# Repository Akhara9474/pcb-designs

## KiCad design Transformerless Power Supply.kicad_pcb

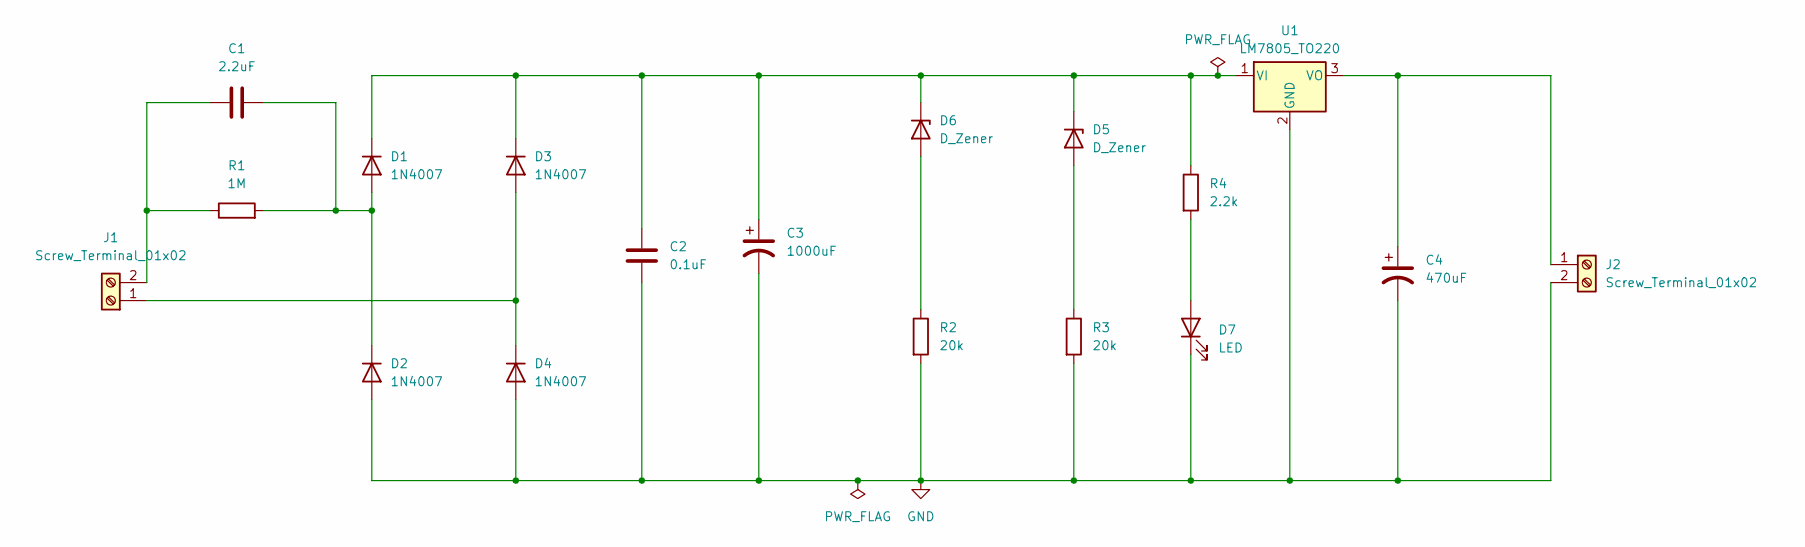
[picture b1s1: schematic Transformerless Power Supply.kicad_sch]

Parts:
C1: 2.2uF; C_Rect_L18.0mm_W6.0mm_P15.00mm_FKS3_FKP3
C2: 0.1uF; C_Disc_D4.7mm_W2.5mm_P5.00mm
C3: 1000uF; CP_Radial_D10.0mm_P5.00mm
C4: 470uF; CP_Radial_D10.0mm_P3.80mm
D1, D2, D3, D4: 1N4007; D_DO-41_SOD81_P10.16mm_Horizontal
D5, D6: D_Zener; D_A-405_P7.62mm_Horizontal
D7: LED; LED_D5.0mm
J1, J2: Screw_Terminal_01x02; Wuerth_691311400102_P7.62mm
R1: 1M; R_Axial_DIN0207_L6.3mm_D2.5mm_P7.62mm_Horizontal
R2, R3: 20k; R_Axial_DIN0207_L6.3mm_D2.5mm_P7.62mm_Horizontal
R4: 2.2k; R_Axial_DIN0207_L6.3mm_D2.5mm_P7.62mm_Horizontal
U1: LM7805_TO220; TO-220-3_Vertical

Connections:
GND: C2.1, C3.2, C4.2, D2.2 (A), D4.2 (A), D7.1 (K), J2.2, R2.2, R3.2, U1.2 (GND)
unnamed: C1.2, D1.2 (A), D2.1 (K), R1.2
unnamed: C2.2, C3.1, D1.1 (K), D3.1 (K), D5.1 (K), D6.1 (K), R4.1, U1.1 (VI)
unnamed: D3.2 (A), D4.1 (K), J1.1
unnamed: D5.2 (A), R3.1
unnamed: D6.2 (A), R2.1
unnamed: D7.2 (A), R4.2
unnamed: C1.1, J1.2, R1.1
unnamed: C4.1, J2.1, U1.3 (VO)

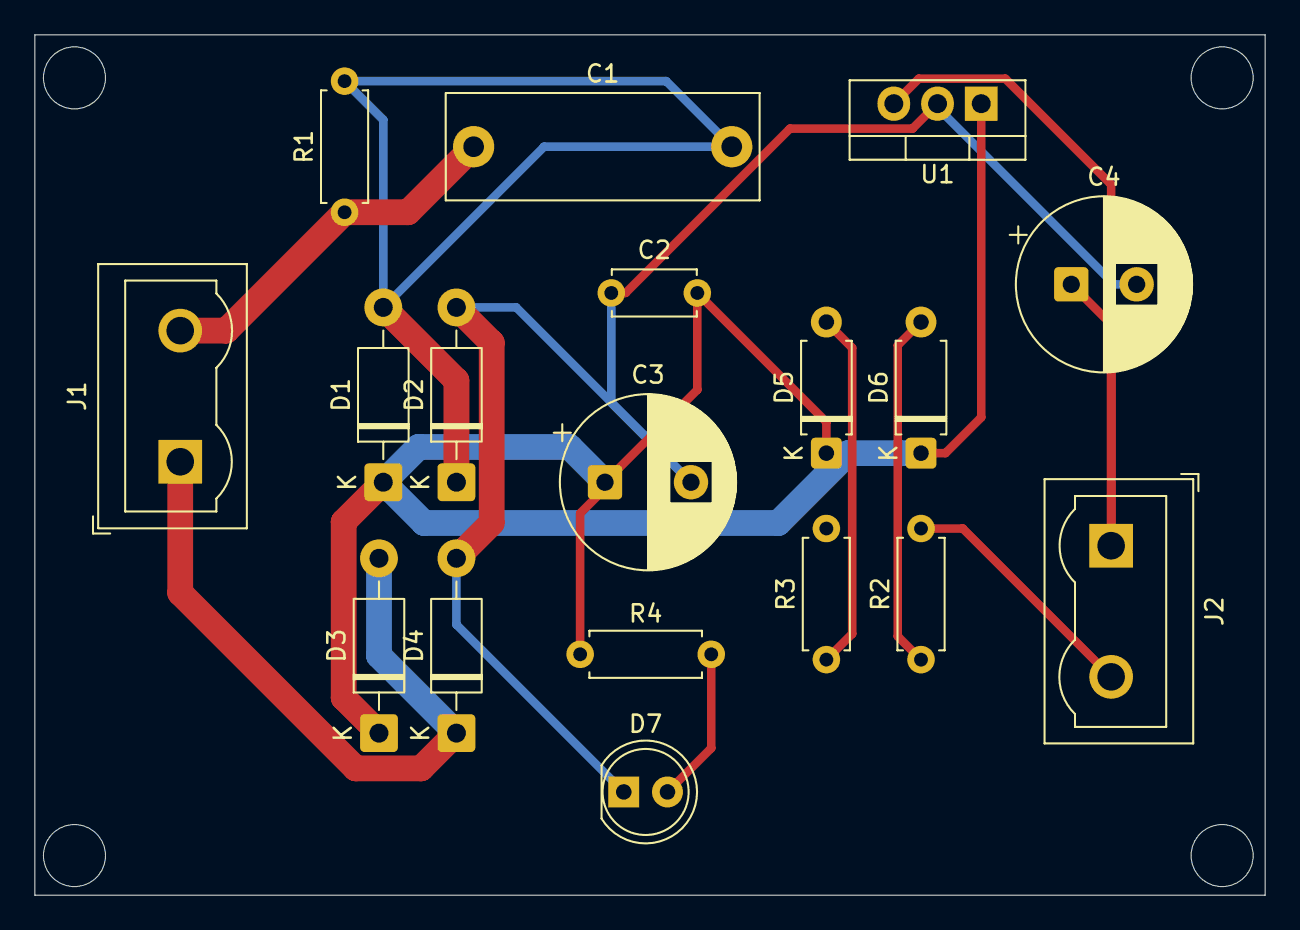
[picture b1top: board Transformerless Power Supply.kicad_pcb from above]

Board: 2 copper layers, 71.5 x 50.0 mm, 18 parts (0 on the bottom side), 9 nets.

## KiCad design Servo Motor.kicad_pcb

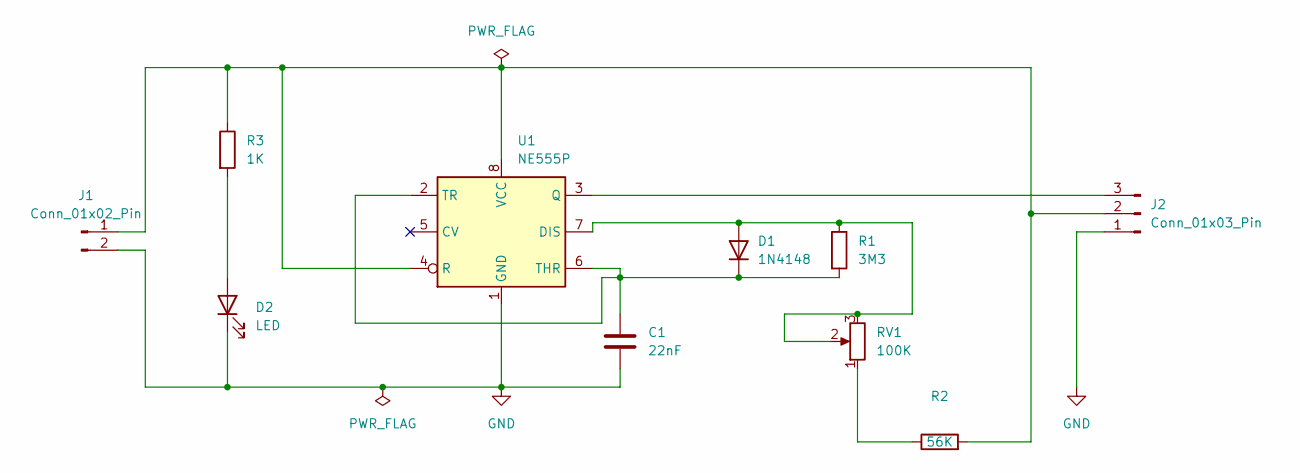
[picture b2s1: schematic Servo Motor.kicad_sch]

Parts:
C1: 22nF; C_Disc_D4.3mm_W1.9mm_P5.00mm
D1: 1N4148; D_DO-35_SOD27_P7.62mm_Horizontal
D2: LED; LED_D3.0mm
J1: Conn_01x02_Pin; PinHeader_1x02_P2.54mm_Horizontal
J2: Conn_01x03_Pin; PinHeader_1x03_P2.54mm_Horizontal
R1: 3M3; R_Axial_DIN0204_L3.6mm_D1.6mm_P7.62mm_Horizontal
R2: 56K; R_Axial_DIN0204_L3.6mm_D1.6mm_P7.62mm_Horizontal
R3: 1K; R_Axial_DIN0204_L3.6mm_D1.6mm_P7.62mm_Horizontal
RV1: 100K; Potentiometer_Alps_RK163_Single_Horizontal
U1: NE555P; DIP-8_W7.62mm

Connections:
GND: C1.1, D2.1 (K), J1.2, J2.1, U1.1 (GND)
unnamed: D1.2 (A), R1.1, RV1.2, RV1.3, U1.7 (DIS)
unnamed: C1.2, D1.1 (K), R1.2, U1.2 (TR), U1.6 (THR)
unnamed: D2.2 (A), R3.2
unnamed: J1.1, J2.2, R2.2, R3.1, U1.4 (R), U1.8 (VCC)
unnamed: J2.3, U1.3 (Q)
unnamed: R2.1, RV1.1

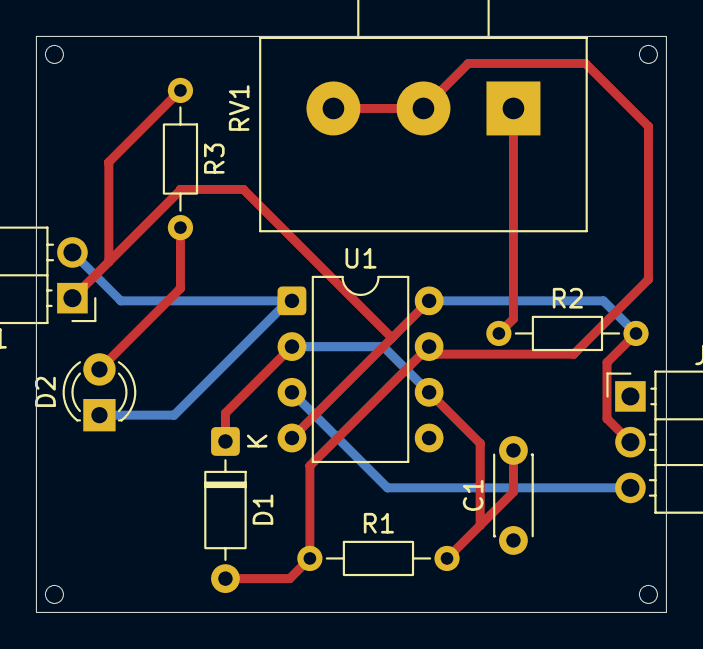
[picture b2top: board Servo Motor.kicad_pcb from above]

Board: 2 copper layers, 35.0 x 32.0 mm, 10 parts (0 on the bottom side), 7 nets.

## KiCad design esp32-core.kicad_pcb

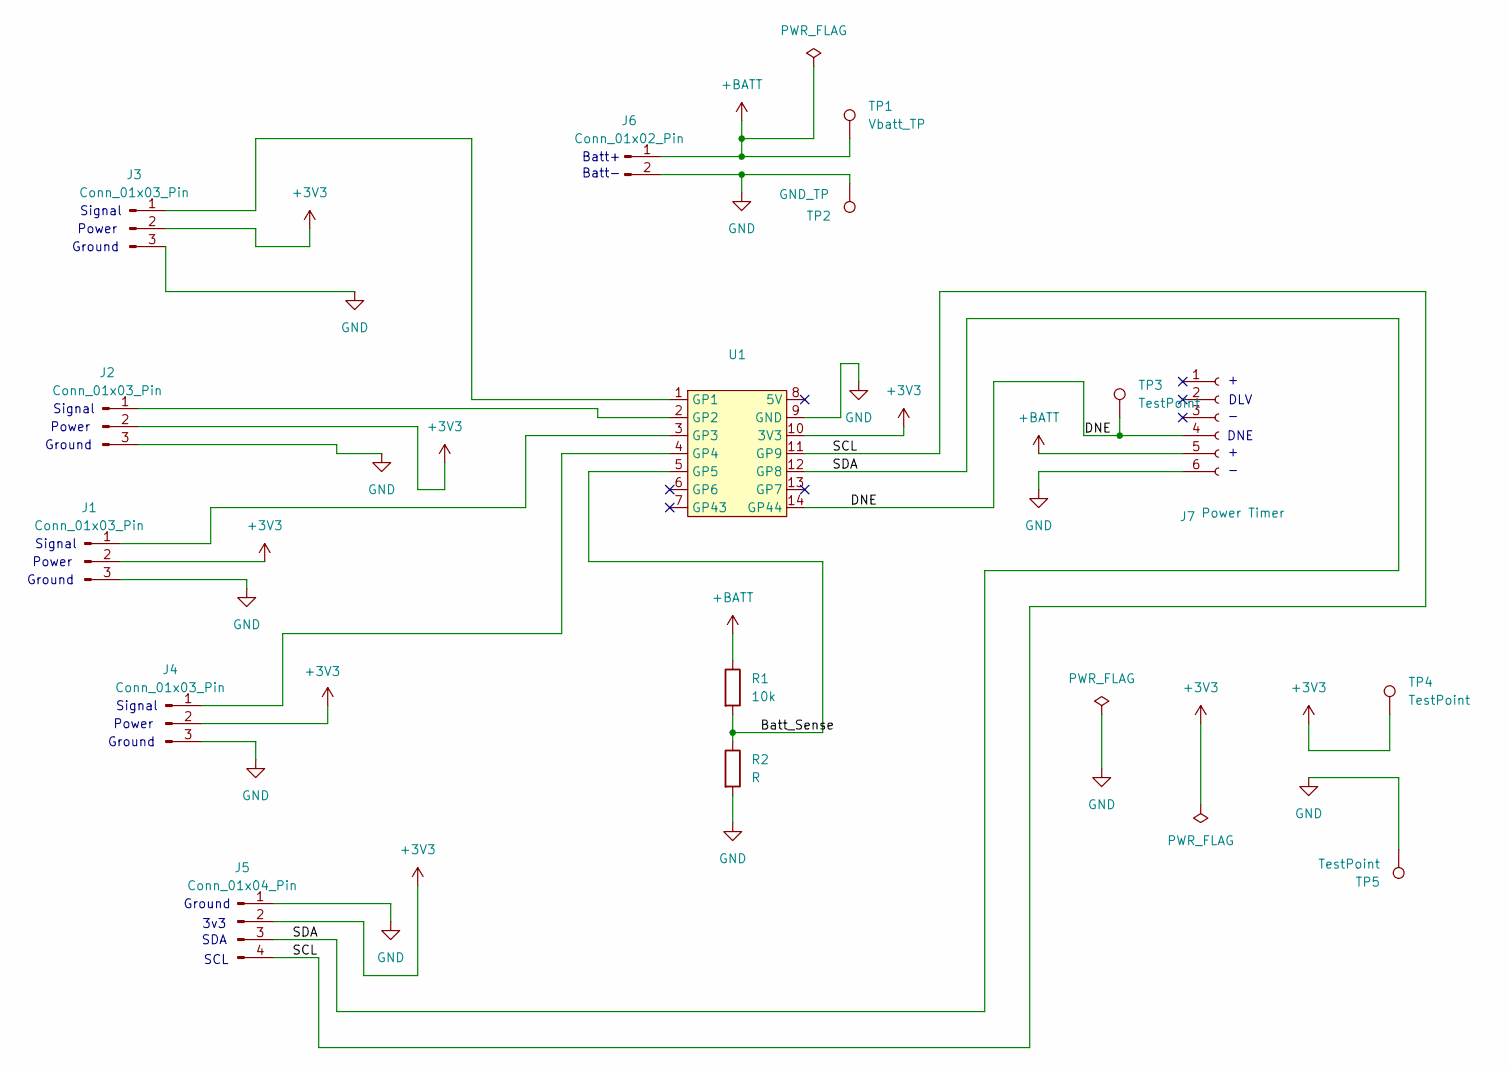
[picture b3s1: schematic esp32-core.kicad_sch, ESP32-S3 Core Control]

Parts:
J1, J2, J3, J4: Conn_01x03_Pin; PinHeader_1x03_P2.54mm_Vertical
J5: Conn_01x04_Pin; PinHeader_1x04_P2.54mm_Vertical
J6: Conn_01x02_Pin; PinHeader_1x02_P2.54mm_Vertical
J7: Power Timer; PinHeader_1x06_P2.54mm_Vertical
R1: 10k; R_Axial_DIN0204_L3.6mm_D1.6mm_P7.62mm_Horizontal
R2: R; R_Axial_DIN0204_L3.6mm_D1.6mm_P7.62mm_Horizontal
TP1: Vbatt_TP; TestPoint_THTPad_1.0x1.0mm_Drill0.5mm
TP2: GND_TP; TestPoint_THTPad_1.0x1.0mm_Drill0.5mm
TP3, TP4, TP5: TestPoint; TestPoint_THTPad_1.0x1.0mm_Drill0.5mm
U1: XIAO-ESP32S3-DIP

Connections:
+3V3: J1.2, J2.2, J3.2, J4.2, J5.2, TP4.1, U1.10 (3V3)
+BATT: J6.1, J7.5, R1.1, TP1.1
/Batt_Sense: R1.2, R2.1, U1.5 (GP5)
/DNE: J7.4, TP3.1, U1.14 (GP44)
/SCL: J5.4, U1.11 (GP9)
/SDA: J5.3, U1.12 (GP8)
GND: J1.3, J2.3, J3.3, J4.3, J5.1, J6.2, J7.6, R2.2, TP2.1, TP5.1, U1.9 (GND)
unnamed: J1.1, U1.3 (GP3)
unnamed: J2.1, U1.2 (GP2)
unnamed: J3.1, U1.1 (GP1)
unnamed: J4.1, U1.4 (GP4)

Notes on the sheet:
Signal
Ground
Power
Batt+
SDA
DLV
DNE
3v3
Batt-
SCL

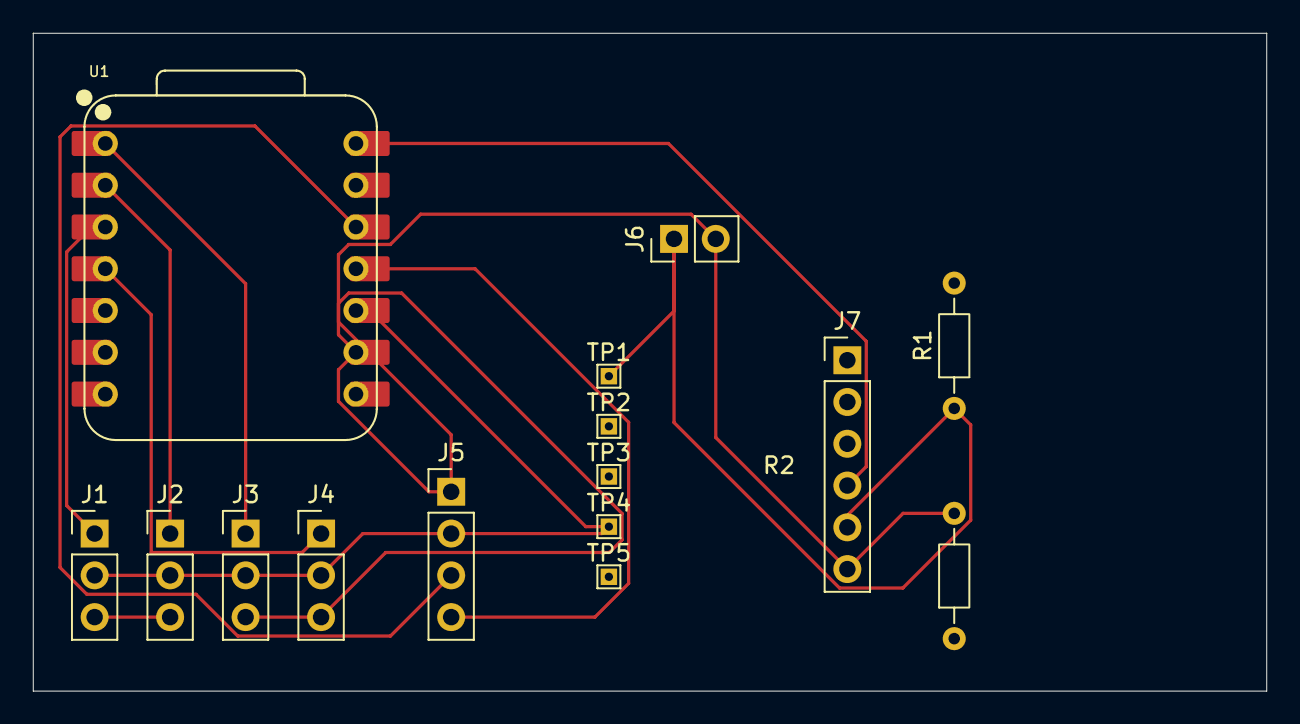
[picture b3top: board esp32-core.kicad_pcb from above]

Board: 2 copper layers, 75.0 x 40.0 mm, 15 parts (0 on the bottom side), 11 nets.

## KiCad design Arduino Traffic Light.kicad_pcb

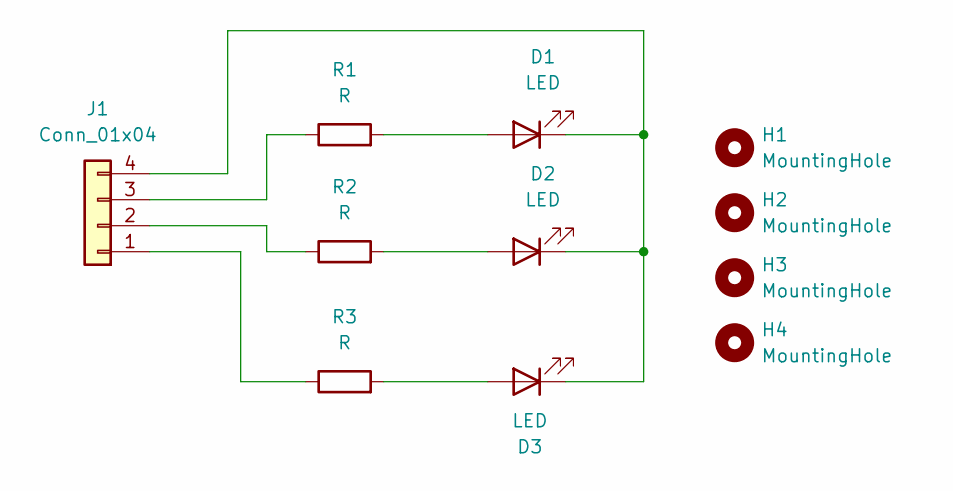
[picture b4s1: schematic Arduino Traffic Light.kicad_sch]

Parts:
D1, D2, D3: LED; LED_D3.0mm
H1, H2, H3, H4: MountingHole; MountingHole_2.5mm_Pad
J1: Conn_01x04; PinHeader_1x04_P2.54mm_Horizontal
R1, R2, R3: R; R_Axial_DIN0204_L3.6mm_D1.6mm_P5.08mm_Vertical

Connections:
unnamed: D1.2 (A), R1.2
unnamed: D1.1 (K), D2.1 (K), D3.1 (K), J1.4
unnamed: D2.2 (A), R2.2
unnamed: D3.2 (A), R3.2
unnamed: J1.1, R3.1
unnamed: J1.2, R2.1
unnamed: J1.3, R1.1

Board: 2 copper layers, 11 parts (0 on the bottom side), 7 nets, no tracks yet.

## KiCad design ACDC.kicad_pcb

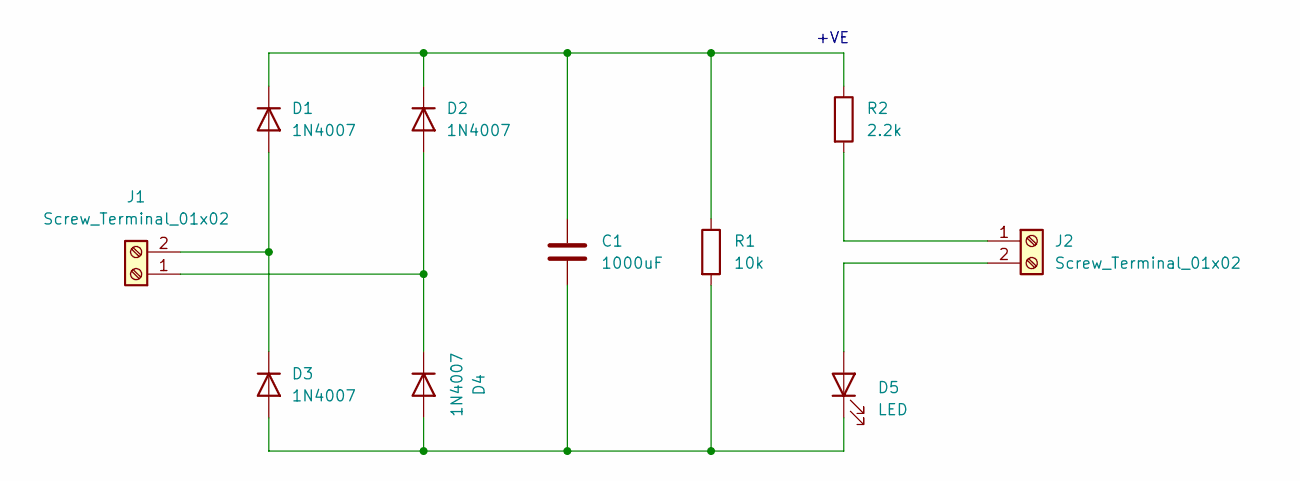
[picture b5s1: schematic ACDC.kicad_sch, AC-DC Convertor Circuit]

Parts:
C1: 1000uF; CP_Radial_D8.0mm_P3.50mm
D1, D2, D3, D4: 1N4007; D_DO-41_SOD81_P10.16mm_Horizontal
D5: LED; LED_D5.0mm
J1, J2: Screw_Terminal_01x02; TerminalBlock_MaiXu_MX126-5.0-02P_1x02_P5.00mm
R1: 10k; R_Axial_DIN0207_L6.3mm_D2.5mm_P7.62mm_Horizontal
R2: 2.2k; R_Axial_DIN0207_L6.3mm_D2.5mm_P7.62mm_Horizontal

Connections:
unnamed: D1.2 (A), D3.1 (K), J1.2
unnamed: C1.1, D1.1 (K), D2.1 (K), R1.1, R2.1
unnamed: D2.2 (A), D4.1 (K), J1.1
unnamed: C1.2, D3.2 (A), D4.2 (A), D5.1 (K), R1.2
unnamed: D5.2 (A), J2.2
unnamed: J2.1, R2.2

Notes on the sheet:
+VE

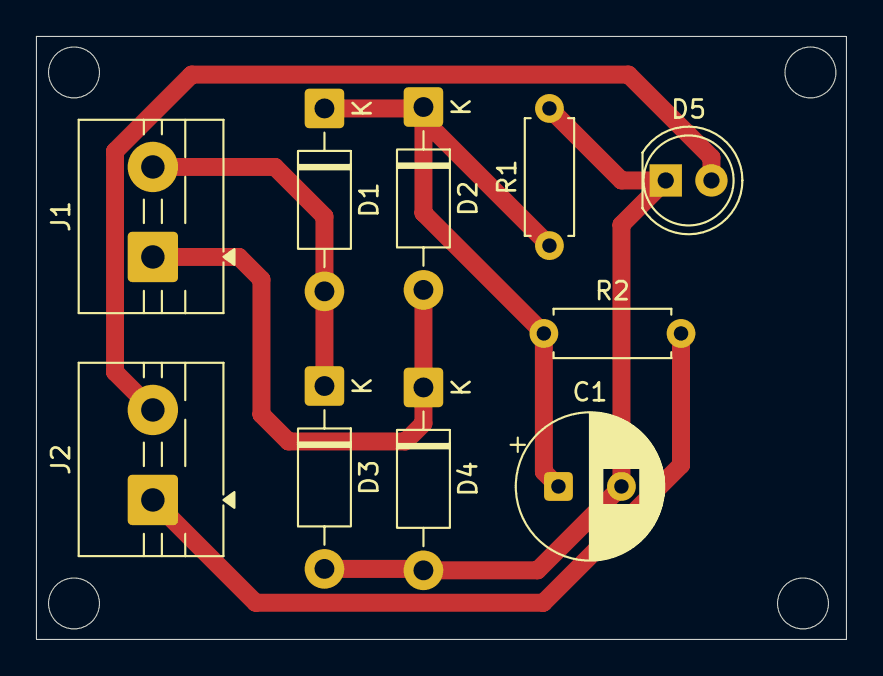
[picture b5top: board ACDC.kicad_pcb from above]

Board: 2 copper layers, 45.0 x 33.5 mm, 10 parts (0 on the bottom side), 6 nets.

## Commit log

2025-12-24 Arduino Nano Replica
